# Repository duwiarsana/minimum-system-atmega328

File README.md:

# minimum-system-atmega328

#Buatan duwiarsana.com

Minimum sistem ini bisa dipakai untuk atmega328, atmega168 dan atmega8
dilengkapi dengan IC ch340 yang dapat dipakai untuk memprogram langsung menggunakan software Arduino IDE

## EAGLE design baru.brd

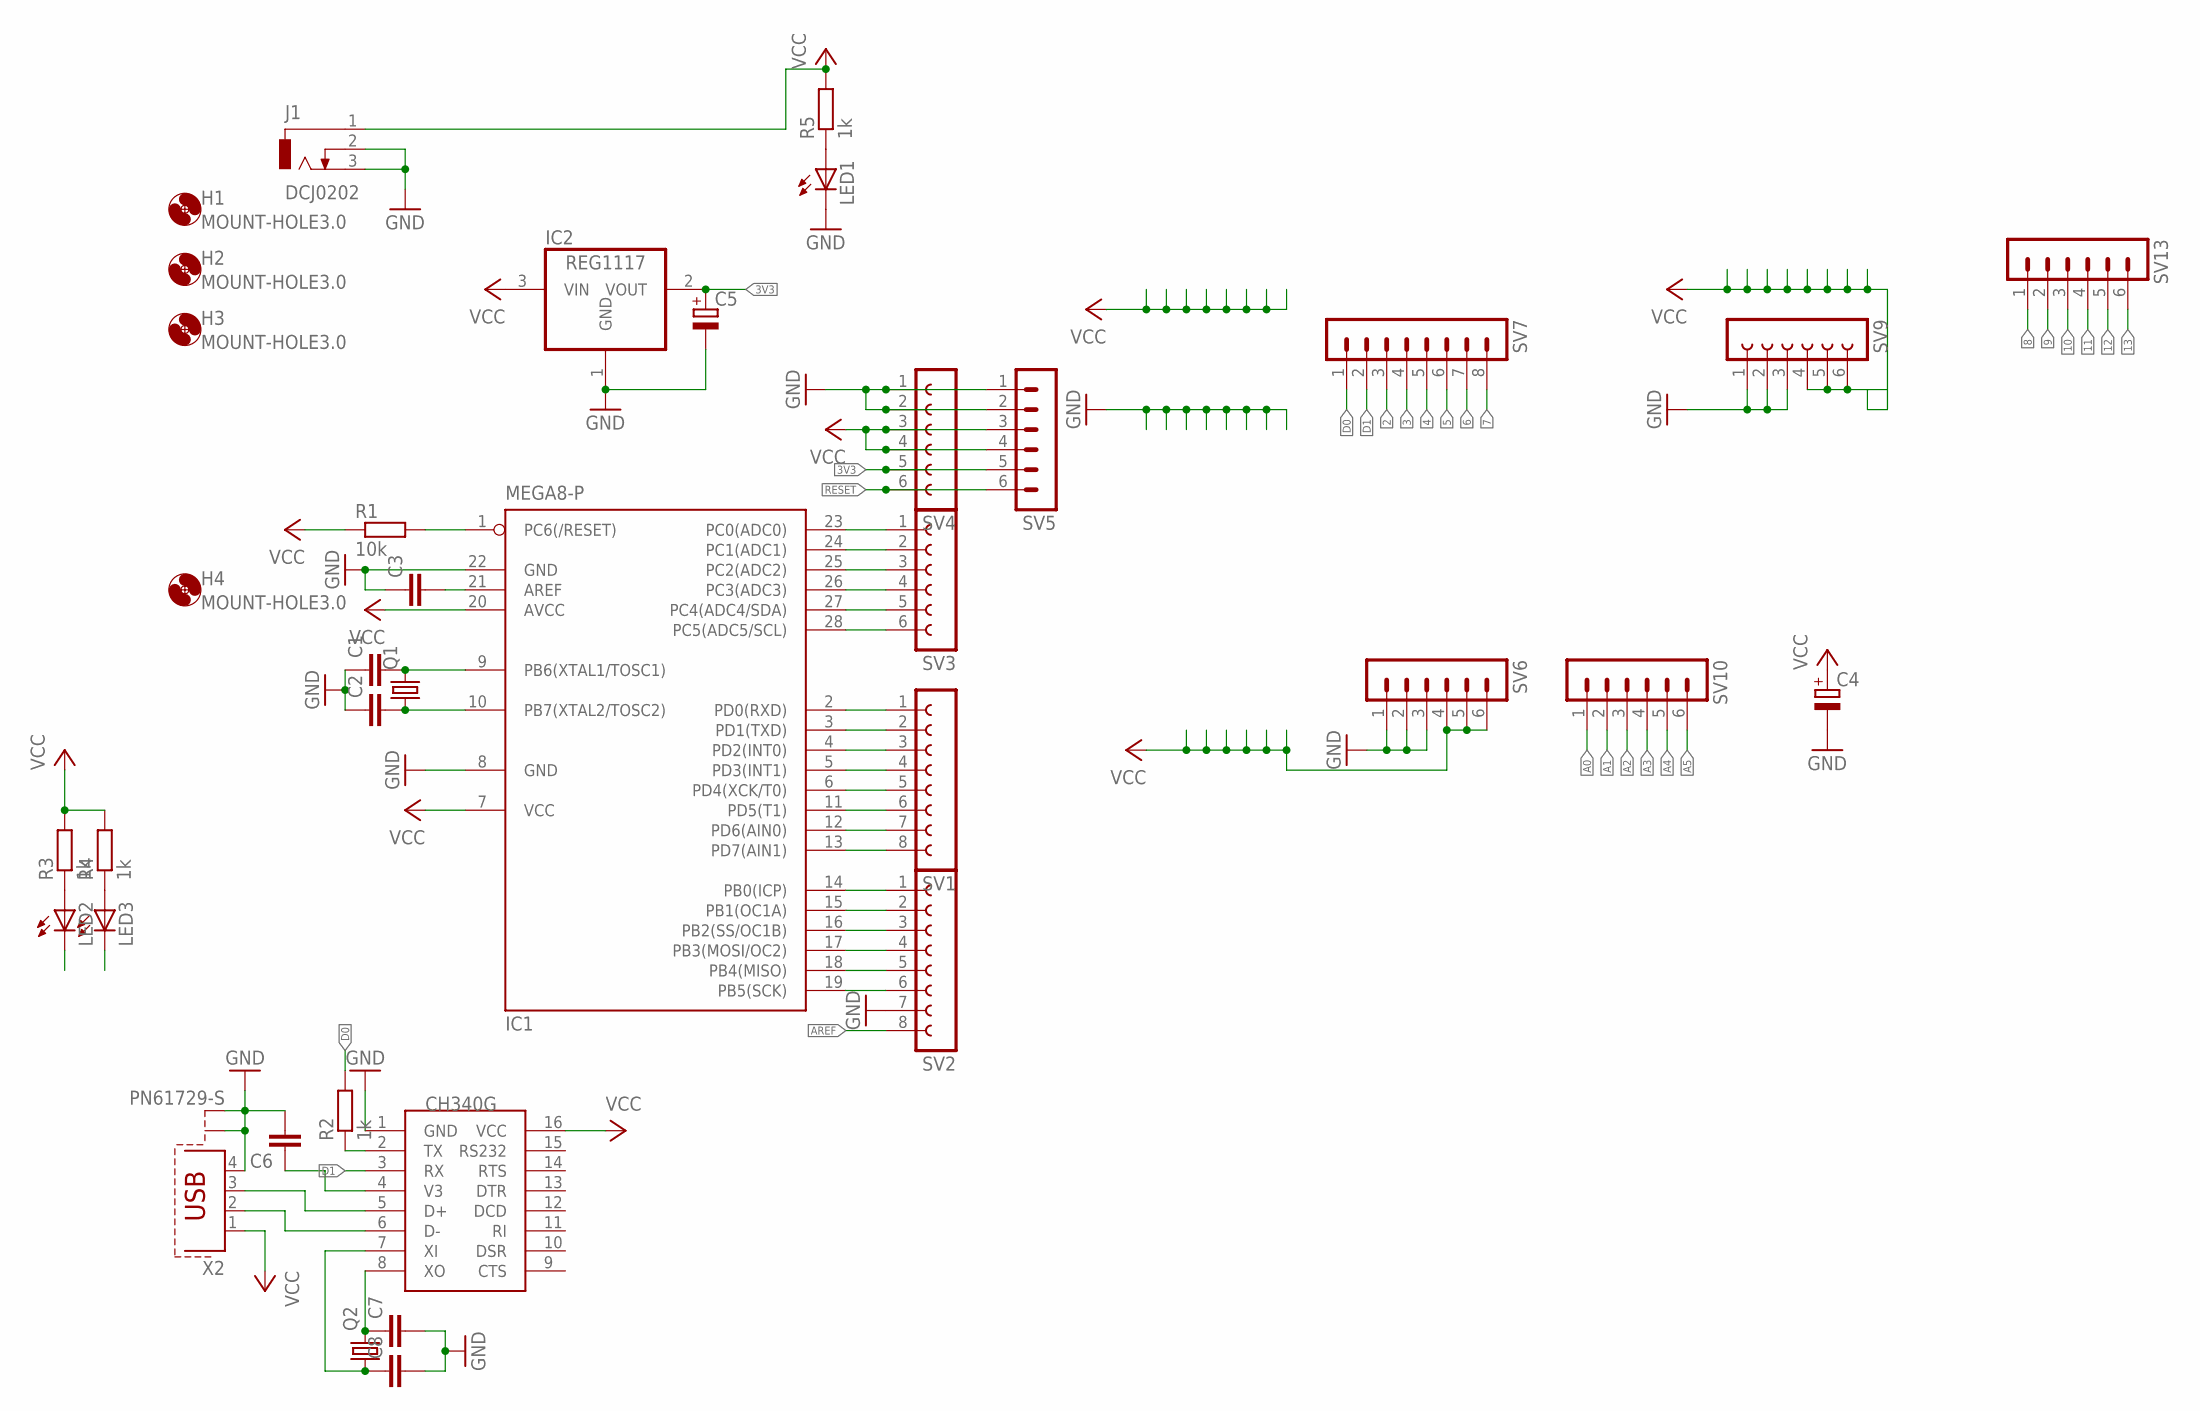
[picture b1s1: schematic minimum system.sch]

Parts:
C1, C2, C7, C8: C-EU025-025X050; C025-025X050
C3, C6: C-EU050-024X044; C050-024X044
C4: CPOL-EUE2.5-7; E2,5-7
C5: CPOL-EUE2.5-5; E2,5-5
H1, H2, H3, H4: MOUNT-HOLE3.0; 3,0
IC1: MEGA8-P; DIL28-3
IC2: REG1117; SOT223
J1: DCJ0202
LED1, LED2, LED3: LED3MM
Q1, Q2: CRYSTALHC49S; HC49/S
R1: 10k; 0207/10
R2, R3, R4, R5: 1k; 0207/10
SV1, SV2: FE08-1; FE08
SV3, SV4, SV9: FE06-1; FE06
SV5, SV6, SV10, SV13: MA06-1
SV7: MA08-1
U$1: CH340G; SOIC16
X2: PN61729-S

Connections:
2: IC1.4 (PD2(INT0)), SV1.3, SV7.3
3: IC1.5 (PD3(INT1)), SV1.4, SV7.4
3V3: C5.+, IC2.2 (VOUT), SV4.5, SV5.5
4: IC1.6 (PD4(XCK/T0)), SV1.5, SV7.5
5: IC1.11 (PD5(T1)), SV1.6, SV7.6
6: IC1.12 (PD6(AIN0)), SV1.7, SV7.7
7: IC1.13 (PD7(AIN1)), SV1.8, SV7.8
8: IC1.14 (PB0(ICP)), SV2.1, SV13.1
9: IC1.15 (PB1(OC1A)), SV2.2, SV13.2
10: IC1.16 (PB2(SS/OC1B)), SV2.3, SV13.3
11: IC1.17 (PB3(MOSI/OC2)), SV2.4, SV13.4
12: IC1.18 (PB4(MISO)), SV2.5, SV13.5
13: IC1.19 (PB5(SCK)), SV2.6, SV13.6
A0: IC1.23 (PC0(ADC0)), SV3.1, SV10.1
A1: IC1.24 (PC1(ADC1)), SV3.2, SV10.2
A2: IC1.25 (PC2(ADC2)), SV3.3, SV10.3
A3: IC1.26 (PC3(ADC3)), SV3.4, SV10.4
A4: IC1.27 (PC4(ADC4/SDA)), SV3.5, SV10.5
A5: IC1.28 (PC5(ADC5/SCL)), SV3.6, SV10.6
AREF: C3.2, IC1.21 (AREF), SV2.8
D0: IC1.2 (PD0(RXD)), R2.2, SV1.1, SV7.1
D1: IC1.3 (PD1(TXD)), LED2.K (C), SV1.2, SV7.2, U$1.3 (RX)
GND: C1.1, C2.1, C3.1, C4.-, C5.-, C6.2, C7.2, C8.2, IC1.8 (GND), IC1.22 (GND), IC2.1 (GND), J1.2, J1.3, LED1.K (C), SV2.7, SV4.1, SV4.2, SV5.1, SV5.2, SV6.1, SV6.2, SV6.3, SV9.1, SV9.2, SV9.3, U$1.1 (GND), X2.4, X2.S1, X2.S2
unnamed: U$1.6 (D-), X2.2
unnamed: U$1.5 (D+), X2.3
unnamed: C1.2, IC1.9 (PB6(XTAL1/TOSC1)), Q1.2
unnamed: C2.2, IC1.10 (PB7(XTAL2/TOSC2)), Q1.1
unnamed: C6.1, U$1.4 (V3)
unnamed: LED2.A, R3.1
unnamed: LED3.A, R4.1
unnamed: LED1.A, R5.1
unnamed: C7.1, Q2.2, U$1.8 (XO)
unnamed: C8.1, Q2.1, U$1.7 (XI)
RESET: IC1.1 (PC6(/RESET)), R1.2, SV4.6, SV5.6
TX: LED3.K (C), R2.1, U$1.2 (TX)
VCC: C4.+, IC1.7 (VCC), IC1.20 (AVCC), IC2.3 (VIN), J1.1, R1.1, R3.2, R4.2, R5.2, SV4.3, SV4.4, SV5.3, SV5.4, SV6.4, SV6.5, SV6.6, SV9.4, SV9.5, SV9.6, U$1.16 (VCC), X2.1

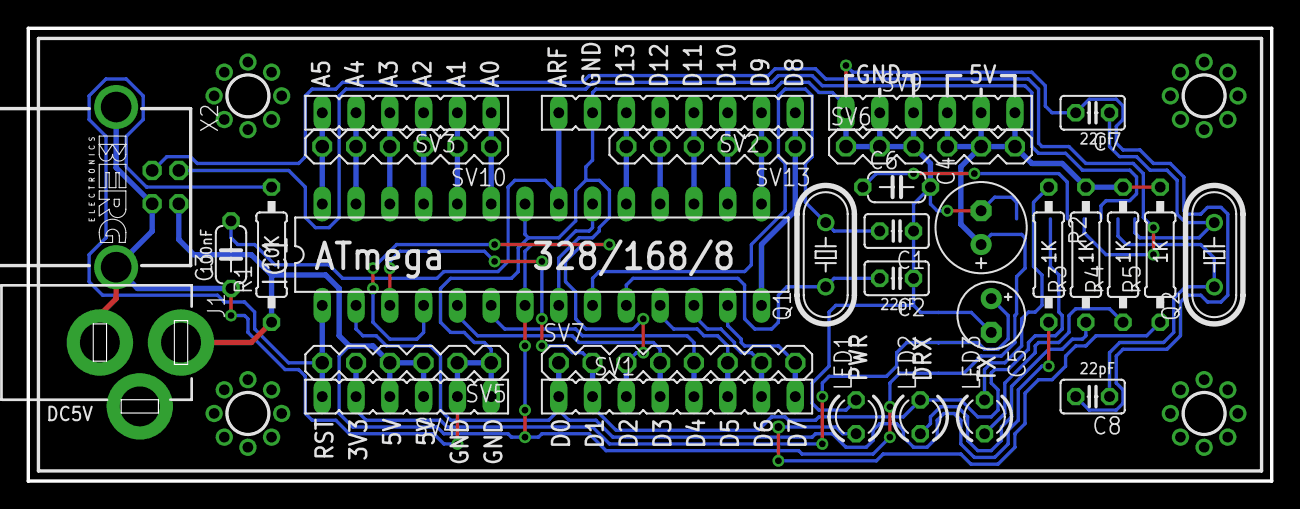
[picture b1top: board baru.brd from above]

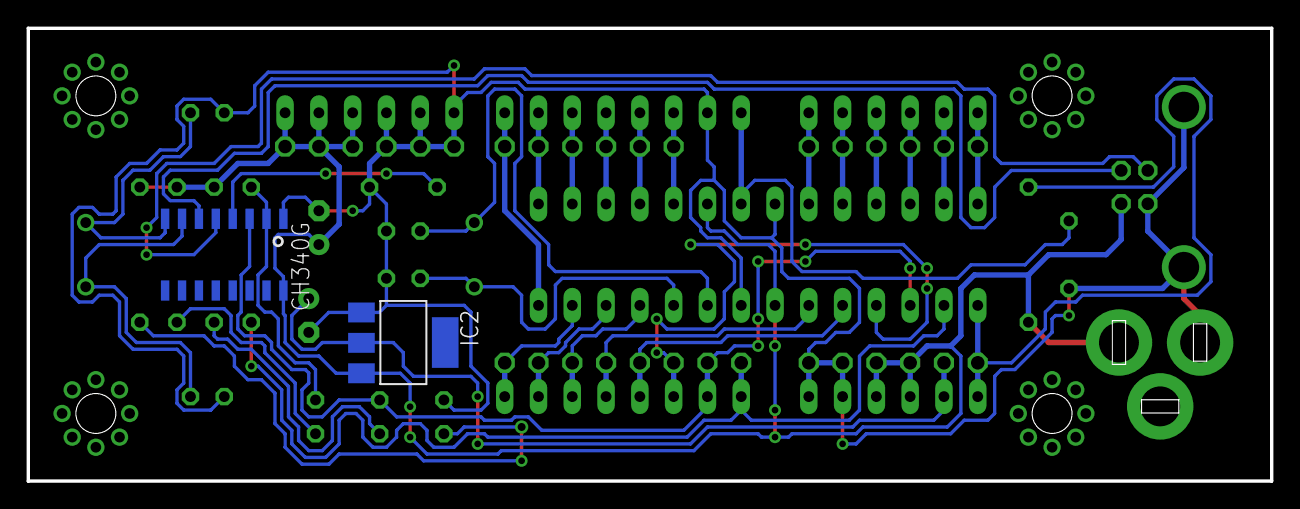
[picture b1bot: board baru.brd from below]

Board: 2 copper layers, 93.5 x 34.0 mm, 37 parts (2 on the bottom side), 36 nets.

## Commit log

2018-06-17 Rename baru.brd to minimum system.brd
2018-06-17 Rename baru.sch to minimum system.sch
